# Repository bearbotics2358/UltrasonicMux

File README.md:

# UltrasonicMux
  This program reads up to 4 Maxbotix ultrasonic sensors and sends
  the output back to the connected computer (CRIO).
  
  The program triggers one sensor at a time and reads its response.
  It waits up to 100 msec for the response.  If none is recevied, it
  substitutes a reading of "999".
  
  A Maxbotix sensor output string example is "R123<CR>".  The program
  substitutes "A", "B", "C", or "D" for the "R", depending on which
  sensor.
  
  The CR is replaced with a TAB for all but the last enabled sensor
  to assist in debugging.
  
  The src/mux subdirectory has the Arduino code for the Ultrasonic Multiplexer.
  
  The src/robot subdirectory has the Sonar class for the robot.

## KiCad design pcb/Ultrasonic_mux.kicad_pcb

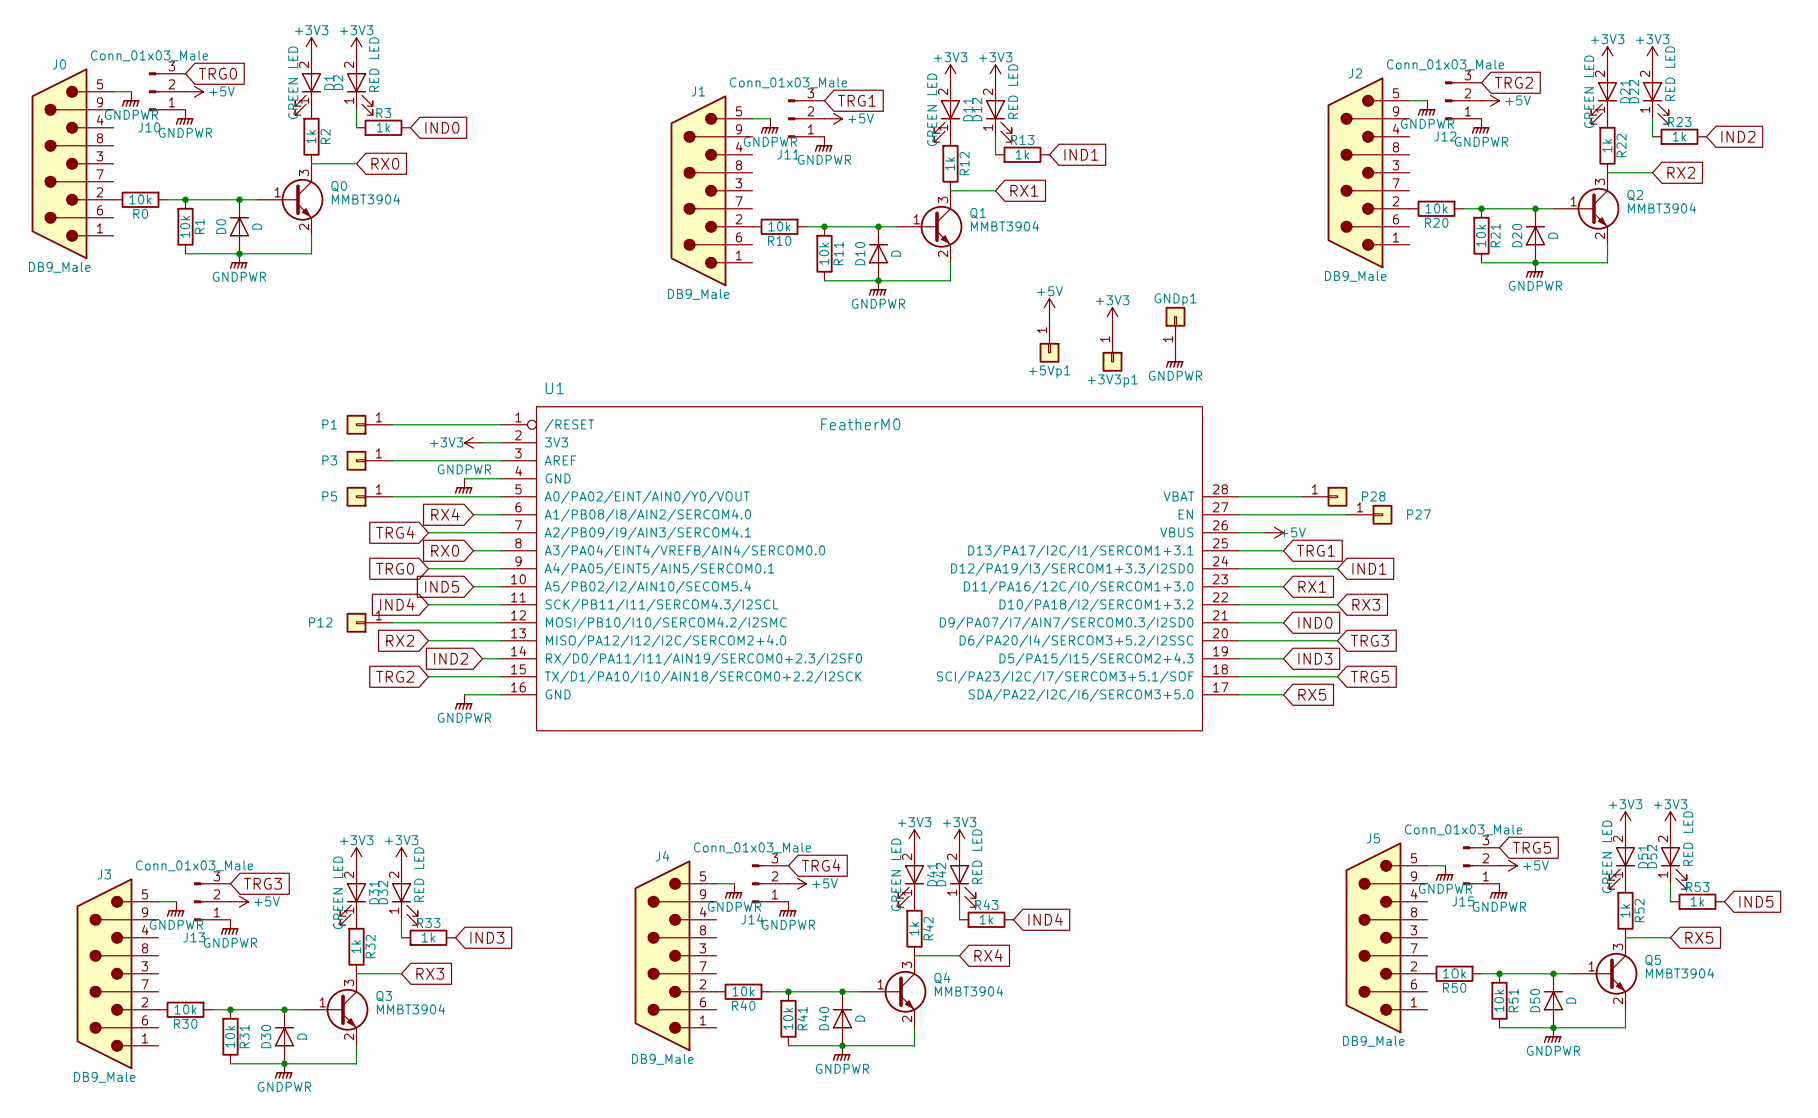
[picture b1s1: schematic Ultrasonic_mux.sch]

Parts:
+3V3p1, +5Vp1: Pin_Header_Straight_1x01_Pitch2.54mm
D0, D10, D20, D30, D40, D50: D; D_SOT-23_ANK
D1, D11, D21, D31, D41, D51: GREEN LED; LED_0805_HandSoldering
D2, D12, D22, D32, D42, D52: RED LED; LED_0603_HandSoldering
GNDp1: Pin_Header_Straight_1x01_Pitch2.54mm
J0, J1, J2, J3, J4, J5: DB9_Male; DSUB-9_Male_Vertical_Pitch2.77x2.84mm_MountingHoles
J10, J11, J12, J13, J14, J15: Conn_01x03_Male; Pin_Header_Straight_1x03_Pitch2.54mm
P1, P3, P5, P12, P27, P28: Pin_Header_Straight_1x01_Pitch2.54mm
Q0, Q1, Q2, Q3, Q4, Q5: MMBT3904; SOT-23
R0, R1, R10, R11, R20, R21, R30, R31, R40, R41, R51: 10k; R_0805_HandSoldering
R2, R3, R12, R13, R22, R23, R32, R33, R42, R43, R52, R53: 1k; R_0805_HandSoldering
R50: 1Ok; R_0805_HandSoldering
U1: FeatherM0; featherm0

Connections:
+3V3: +3V3p1.1, D1.2 (A), D2.2 (A), D11.2 (A), D12.2 (A), D21.2 (A), D22.2 (A), D31.2 (A), D32.2 (A), D41.2 (A), D42.2 (A), D51.2 (A), D52.2 (A), U1.2 (3V3)
+5V: +5Vp1.1, J10.2, J11.2, J12.2, J13.2, J14.2, J15.2, U1.26 (VBUS)
GNDPWR: D0.2 (A), D10.2 (A), D20.2 (A), D30.2 (A), D40.2 (A), D50.2 (A), GNDp1.1, J0.5, J1.5, J2.5, J3.5, J4.5, J5.5, J10.1, J11.1, J12.1, J13.1, J14.1, J15.1, Q0.2 (E), Q1.2 (E), Q2.2 (E), Q3.2 (E), Q4.2 (E), Q5.2 (E), R1.1, R11.1, R21.1, R31.1, R41.1, R51.1, U1.4 (GND), U1.16 (GND)
IND0: R3.1, U1.21 (D9/PA07/I7/AIN7/SERCOM0.3/I2SD0)
IND1: R13.1, U1.24 (D12/PA19/I3/SERCOM1+3.3/I2SD0)
IND2: R23.1, U1.14 (RX/D0/PA11/I11/AIN19/SERCOM0+2.3/I2SF0)
IND3: R33.1, U1.19 (D5/PA15/I15/SERCOM2+4.3)
IND4: R43.1, U1.11 (SCK/PB11/I11/SERCOM4.3/I2SCL)
IND5: R53.1, U1.10 (A5/PB02/I2/AIN10/SECOM5.4)
unnamed: D0.1 (K), Q0.1 (B), R0.2, R1.2
unnamed: D1.1 (K), R2.2
unnamed: D2.1 (K), R3.2
unnamed: D10.1 (K), Q1.1 (B), R10.2, R11.2
unnamed: D11.1 (K), R12.2
unnamed: D12.1 (K), R13.2
unnamed: D20.1 (K), Q2.1 (B), R20.2, R21.2
unnamed: D21.1 (K), R22.2
unnamed: D22.1 (K), R23.2
unnamed: D30.1 (K), Q3.1 (B), R30.2, R31.2
unnamed: D31.1 (K), R32.2
unnamed: D32.1 (K), R33.2
unnamed: D40.1 (K), Q4.1 (B), R40.2, R41.2
unnamed: D41.1 (K), R42.2
unnamed: D42.1 (K), R43.2
unnamed: D50.1 (K), Q5.1 (B), R50.2, R51.2
unnamed: D51.1 (K), R52.2
unnamed: D52.1 (K), R53.2
unnamed: J0.2, R0.1
unnamed: J1.2, R10.1
unnamed: J2.2, R20.1
unnamed: J3.2, R30.1
unnamed: J4.2, R40.1
unnamed: J5.2, R50.1
unnamed: P1.1, U1.1 (/RESET)
unnamed: P3.1, U1.3 (AREF)
unnamed: P5.1, U1.5 (A0/PA02/EINT/AIN0/Y0/VOUT)
unnamed: P12.1, U1.12 (MOSI/PB10/I10/SERCOM4.2/I2SMC)
unnamed: P27.1, U1.27 (EN)
unnamed: P28.1, U1.28 (VBAT)
RX0: Q0.3 (C), R2.1, U1.8 (A3/PA04/EINT4/VREFB/AIN4/SERCOM0.0)
RX1: Q1.3 (C), R12.1, U1.23 (D11/PA16/12C/I0/SERCOM1+3.0)
RX2: Q2.3 (C), R22.1, U1.13 (MISO/PA12/I12/I2C/SERCOM2+4.0)
RX3: Q3.3 (C), R32.1, U1.22 (D10/PA18/I2/SERCOM1+3.2)
RX4: Q4.3 (C), R42.1, U1.6 (A1/PB08/I8/AIN2/SERCOM4.0)
RX5: Q5.3 (C), R52.1, U1.17 (SDA/PA22/I2C/I6/SERCOM3+5.0)
TRG0: J10.3, U1.9 (A4/PA05/EINT5/AIN5/SERCOM0.1)
TRG1: J11.3, U1.25 (D13/PA17/I2C/I1/SERCOM1+3.1)
TRG2: J12.3, U1.15 (TX/D1/PA10/I10/AIN18/SERCOM0+2.2/I2SCK)
TRG3: J13.3, U1.20 (D6/PA20/I4/SERCOM3+5.2/I2SSC)
TRG4: J14.3, U1.7 (A2/PB09/I9/AIN3/SERCOM4.1)
TRG5: J15.3, U1.18 (SCI/PA23/I2C/I7/SERCOM3+5.1/SOF)

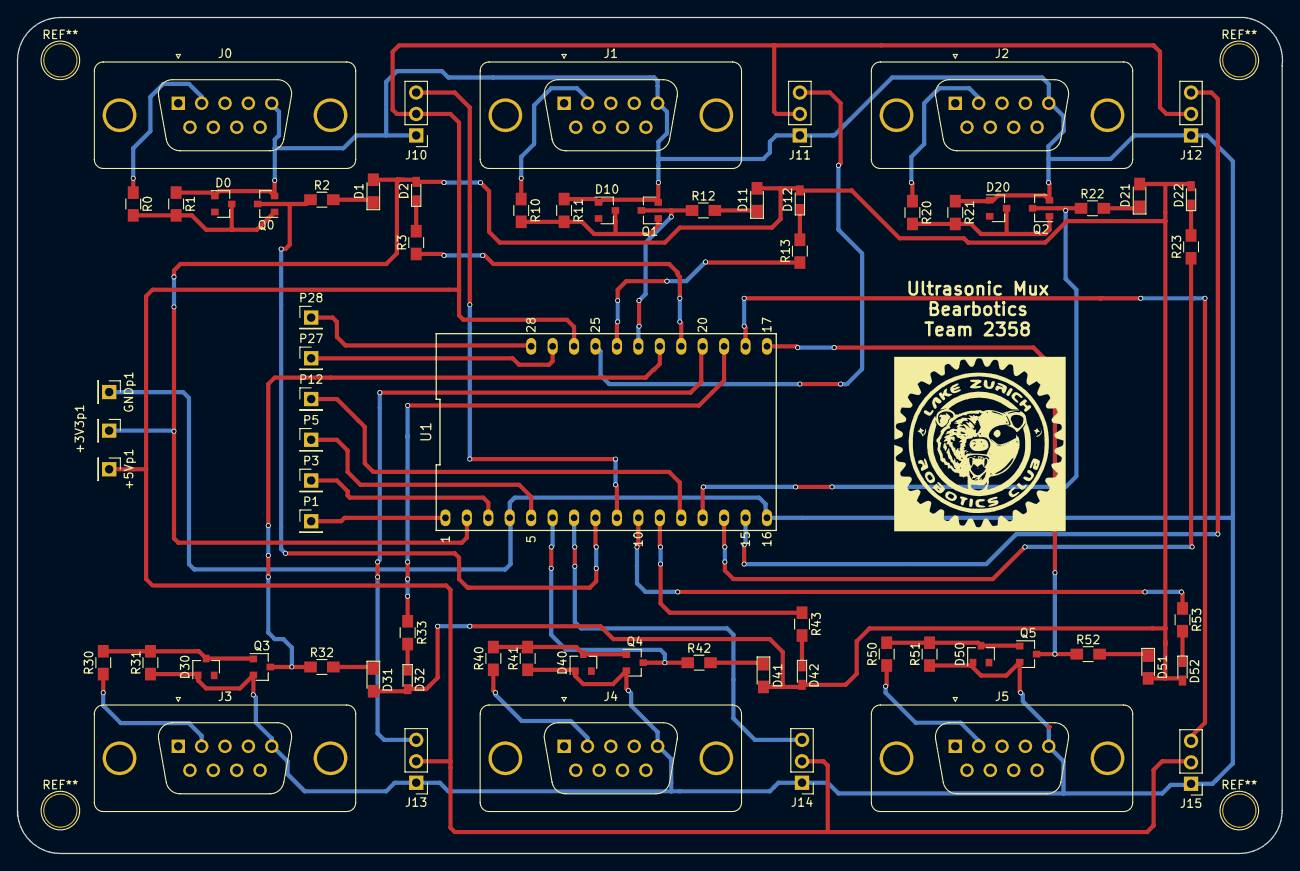
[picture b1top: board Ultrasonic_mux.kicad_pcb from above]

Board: 2 copper layers, 149.9 x 99.1 mm, 70 parts (0 on the bottom side), 51 nets.

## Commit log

2018-01-13 Change directory structure Add Sonar class for robot
2018-01-27 Added pcb Folder Changed file structure to make Arduino happy Changed parser to support simultaneous operation
2018-01-27 Actually added pcb folder
2018-01-27 Working on FeatherM0 schematic symbol
2018-01-29 finished schematic for pcb
2018-01-29 Added titles
2018-01-30 Creating schematic.
2018-01-31 Finished RX ports and finished 3-pin connectors and power.
2018-02-01 Getting rid of ports 7 and 8, starting to label indicators/triggers.
2018-02-01 Finished labeling indicators/triggers and organized layout.
2018-02-02 References
2018-02-02 Changed voltage
2018-02-03 Finished schematic
2018-02-03 Added netlist restarted footprint associations for board
2018-02-03 Finished footprints, starting layout of board.
2018-02-03 Organized layout.
2018-02-03 Hopefully finished track routes.
2018-02-05 BD: Reduced board size to 150x100mm for easier fit on 'bot, and reduced mechanical stress. Added vias to permit easier mods (runner cuts and soldered wire reconnect to another pad/circuit)
    It still thinks 5v is not connected!
    Tried replacing connecting segments to J13 and U1
    Tried adding another trace to each on bottom of board
2018-02-05 Added logo and text Still an issue with the 5v connection Order is based on gerber's, so shouldn't be a problem Worst case, small jumper wire Created gerber files
2018-02-05 Now with the gerber files
2018-02-07 no message
2018-02-08 Checked layout, doesn't look like anything is wrong.
2018-02-17 Add SAMD21_serial.ino test routine All 6 serial ports working
    Unknown change to the pcb project
    Added some data sheets
2018-02-17 All 6 sensors operating in parallel Output string format is as in the former mux
